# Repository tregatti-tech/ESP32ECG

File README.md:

# ESP32ECG
Open design/code version of ECG device based on esp32

Website https://tregatti.tech
Email info@

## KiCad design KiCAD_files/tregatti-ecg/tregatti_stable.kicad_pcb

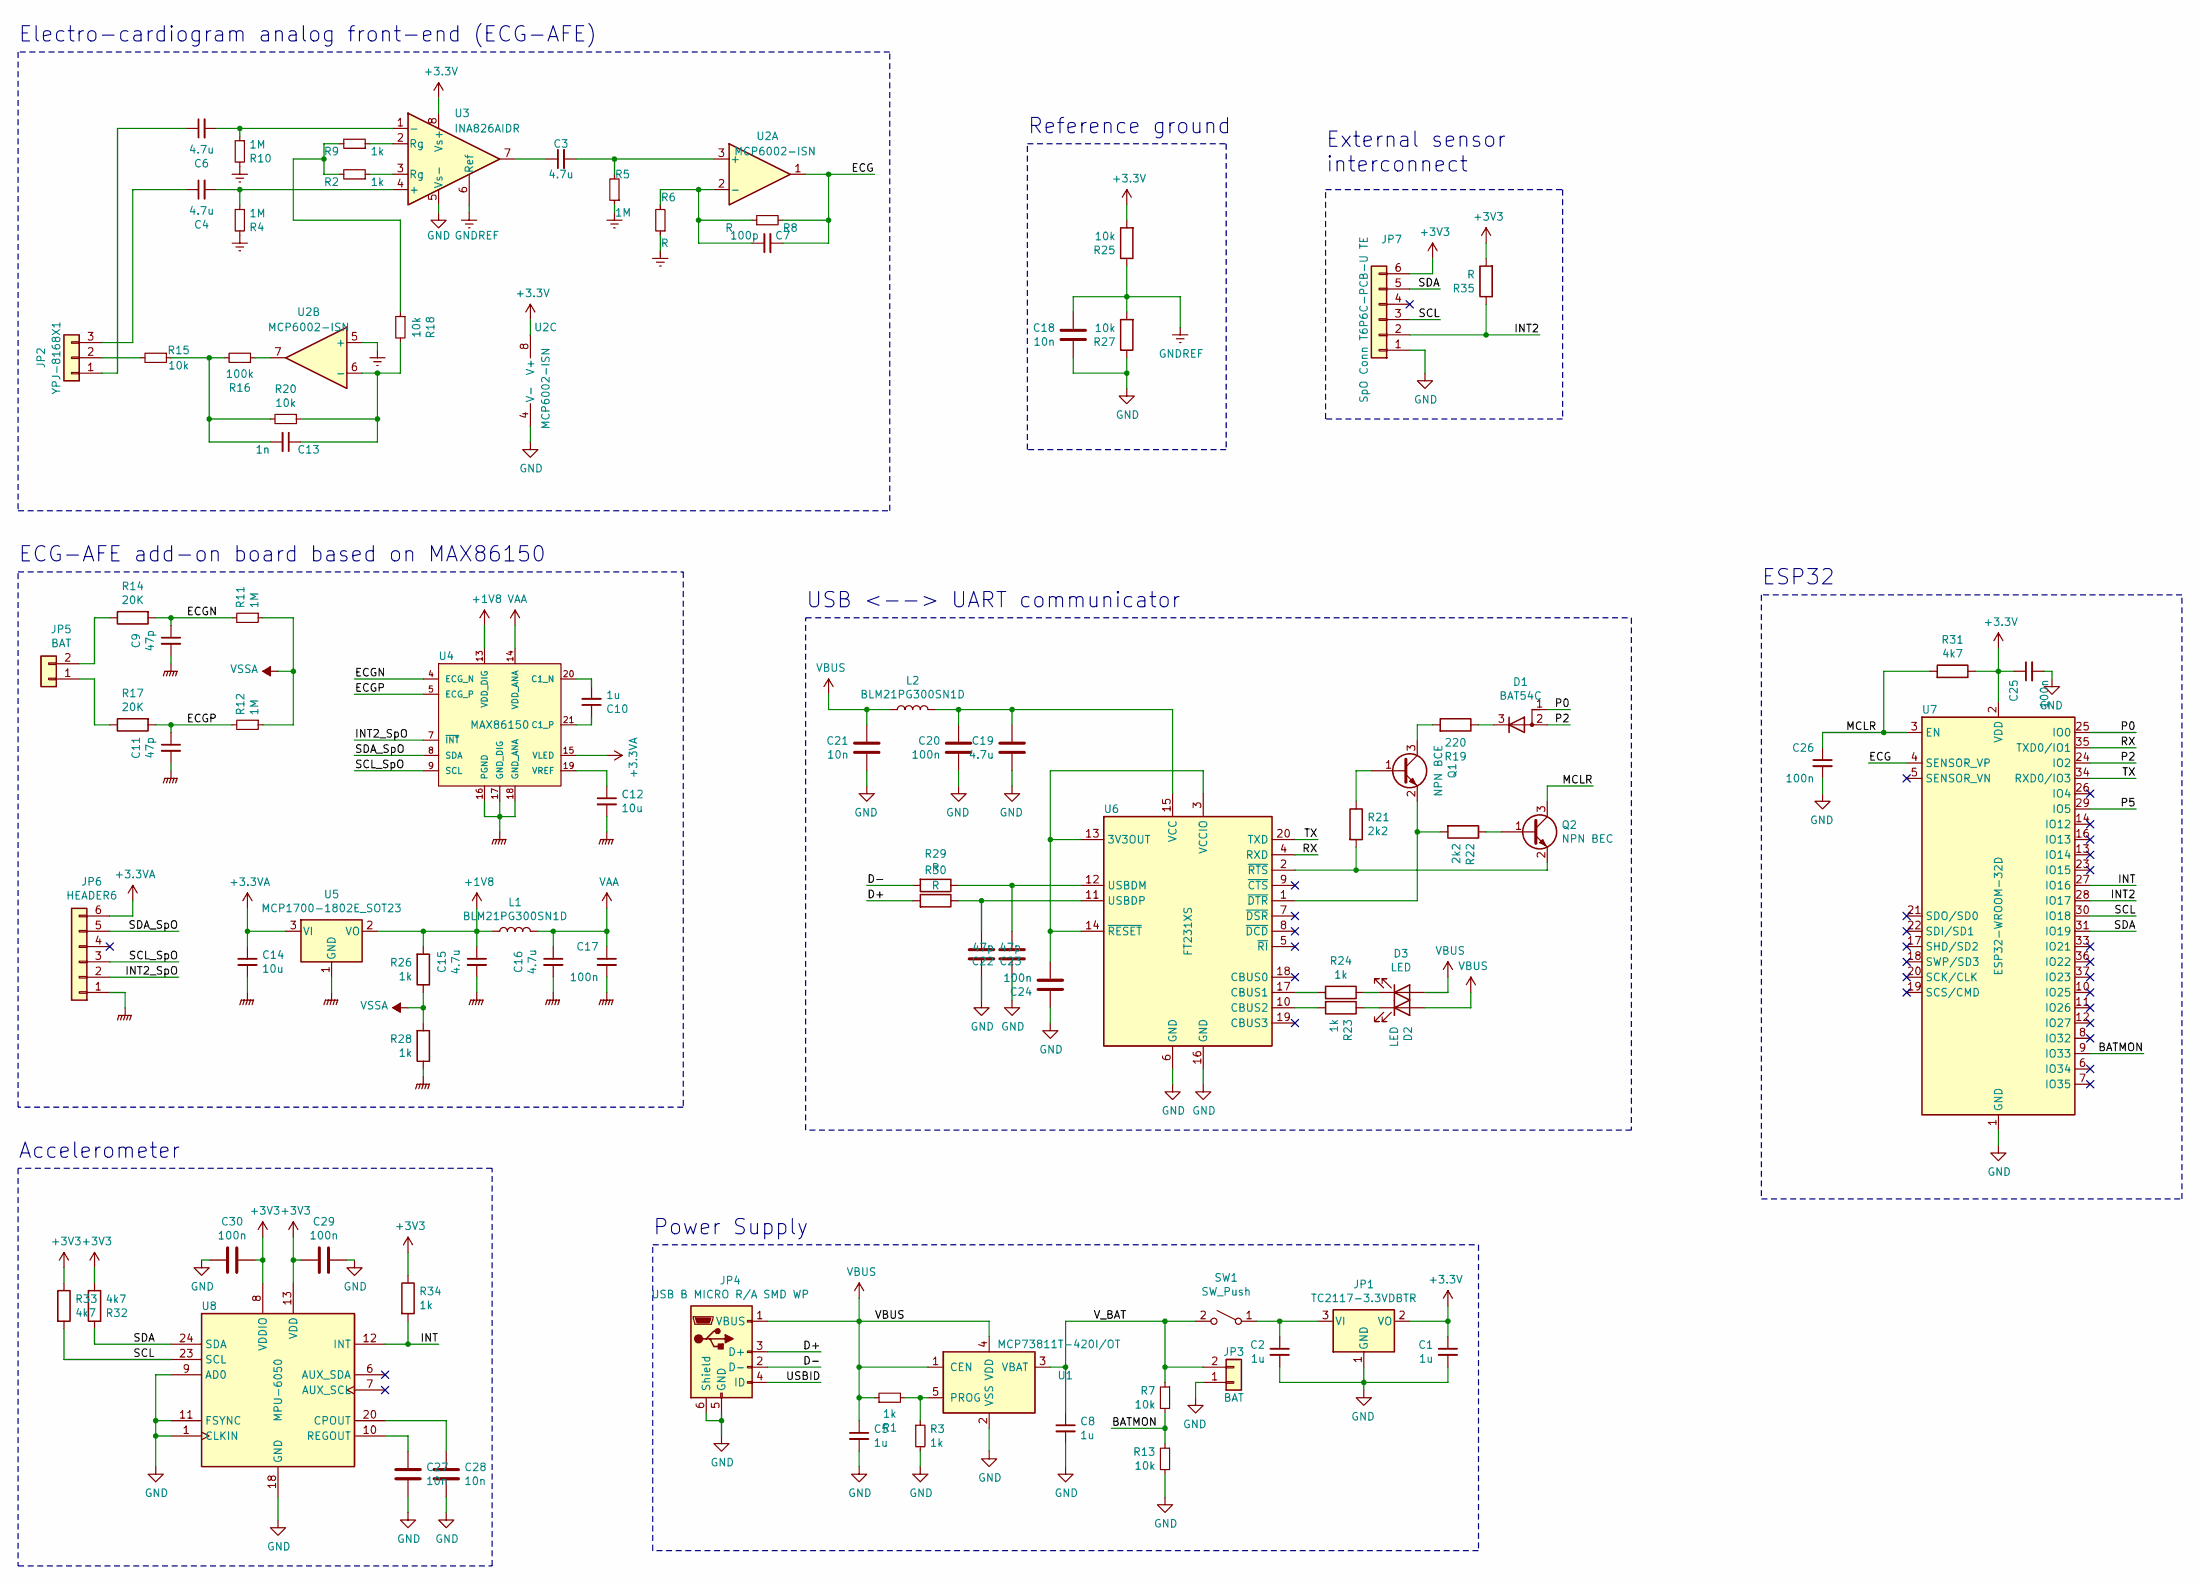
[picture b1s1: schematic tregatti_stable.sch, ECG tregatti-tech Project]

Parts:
C1, C2, C5, C8, C10: 1u; SMD_C0805
C3, C4, C6, C15, C16, C19: 4.7u; SMD_C0805
C7: 100p; SMD_C0805
C9, C11, C22, C23: 47p; SMD_C0805
C12, C14: 10u; SMD_C0805
C13: 1n; SMD_C0805
C17, C20, C24, C25, C26, C29, C30: 100n; SMD_C0805
C18, C21, C27, C28: 10n; SMD_C0805
D1: BAT54C; SMD_SOT23_123
D2, D3: LED; SMD_LED0805
JP1: TC2117-3.3VDBTR; SMD_SOT223
JP2: YPJ-8168X1; AUX_IN_3_5MM_2
JP3, JP5: BAT; SIP_1x2
JP4: USB B MICRO R/A SMD WP; USB_MICRO3
JP6: HEADER6; SIP_1x6
JP7: SpO Conn T6P6C-PCB-U TE; TM.310FACE_6X6
L1, L2: BLM21PG300SN1D; SMD_R0805
Q1: NPN BCE; SMD_SOT23_123
Q2: NPN BEC; SMD_SOT23_123
R1, R2, R3, R9, R23, R24, R26, R28, R34: 1k; SMD_R0805
R4, R5, R10, R11, R12: 1M; SMD_R0805
R6, R8, R29, R30, R35: R; SMD_R0805
R7, R13, R15, R18, R20, R25, R27: 10k; SMD_R0805
R14, R17: 20K; SMD_R0805
R16: 100k; SMD_R0805
R19: 220; SMD_R0805
R21, R22: 2k2; SMD_R0805
R31, R32, R33: 4k7; SMD_R0805
SW1: SW_Push; SWITCH_ONOFF
U1: MCP73811T-420I/OT; SMD_SOT23_5
U2: MCP6002-ISN; SO8_3.9x4.9mm_P1.27mm
U3: INA826AIDR; SO8_3.9x4.9mm_P1.27mm
U4: MAX86150
U5: MCP1700-1802E_SOT23; SMD_SOT23_123
U6: FT231XS; SSOP20_3.9x8.7mm_P0.635mm
U7: ESP32-WROOM-32D; ESP32WROOM
U8: MPU-6050; QFN24_0.50mm_EP4.00mm

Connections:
+1V8: C15.1, L1.1, R26.2, U4.13 (VDD_DIG), U5.2 (VO)
+3.3VA: C14.1, JP6.6, U4.15 (VLED), U5.3 (VI)
/BATMON: R7.2, R13.1, U7.9 (IO33)
/D+: JP4.3 (D+), R30.2
/D-: JP4.2 (D-), R29.2
/ECG: C7.2, R8.2, U2.1, U7.4 (SENSOR_VP)
/ECGN: C9.1, R11.2, R14.2, U4.4 (ECG_N)
/ECGP: C11.1, R12.2, R17.2, U4.5 (ECG_P)
/INT: R34.2, U7.27 (IO16), U8.12 (INT)
/INT2: JP7.2, R35.1, U7.28 (IO17)
/INT2_SpO: JP6.2, U4.7 (~INT~)
/MCLR: C26.1, Q2.3 (C), R31.2, U7.3 (EN)
/P0: D1.1 (A), U7.25 (IO0)
/P2: D1.2 (A), U7.24 (IO2)
/P5: U7.29 (IO5)
/RX: U6.4 (RXD), U7.35 (TXD0/IO1)
/SCL: JP7.3, R33.2, U7.30 (IO18), U8.23 (SCL)
/SCL_SpO: JP6.3, U4.9 (SCL)
/SDA: JP7.5, R32.2, U7.31 (IO19), U8.24 (SDA)
/SDA_SpO: JP6.5, U4.8 (SDA)
/TX: U6.20 (TXD), U7.34 (RXD0/IO3)
/USBID: JP4.4 (ID)
/V_BAT: C8.1, JP3.2, R7.1, SW1.2 (B), U1.3 (VBAT)
GND: C1.2, C2.2, C5.2, C8.2, C18.2, C19.2, C20.2, C21.2, C22.2, C23.2, C24.2, C25.2, C26.2, C27.2, C28.2, C29.2, C30.2, JP1.1 (GND), JP3.1, JP4.5 (GND), JP4.6 (Shield), JP7.1, R3.2, R13.2, R27.1, U1.2 (VSS), U2.4 (V-), U3.5 (Vs-), U6.6 (GND), U6.16 (GND), U7.1 (GND), U7.15 (GND), U7.38 (GND), U7.39 (GND), U8.1 (CLKIN), U8.9 (AD0), U8.11 (FSYNC), U8.18 (GND)
GNDPWR: C9.2, C11.2, C12.2, C14.2, C15.2, C16.2, C17.2, JP6.1, R28.1, U4.16 (PGND), U4.17 (GND_DIG), U4.18 (GND_ANA), U5.1 (GND)
GNDREF: C18.1, R4.2, R5.1, R6.1, R10.2, R25.1, R27.2, U2.5 (+), U3.6 (Ref)
unnamed: C2.1, JP1.3 (VI), SW1.1 (A)
unnamed: C3.1, U3.7
unnamed: C3.2, R5.2, U2.3 (+)
unnamed: C4.1, JP2.3
unnamed: C4.2, R4.1, U3.4 (+)
unnamed: C6.1, JP2.1
unnamed: C6.2, R10.1, U3.1 (-)
unnamed: C7.1, R6.2, R8.1, U2.2 (-)
unnamed: C10.1, U4.21 (C1_P)
unnamed: C10.2, U4.20 (C1_N)
unnamed: C12.1, U4.19 (VREF)
unnamed: C13.1, R18.2, R20.1, U2.6 (-)
unnamed: C13.2, R15.1, R16.2, R20.2
unnamed: C19.1, C20.1, L2.1, U6.15 (VCC)
unnamed: C22.1, R29.1, U6.12 (USBDM)
unnamed: C23.1, R30.1, U6.11 (USBDP)
unnamed: C24.1, U6.3 (VCCIO), U6.13 (3V3OUT), U6.14 (~RESET)
unnamed: C27.1, U8.10 (REGOUT)
unnamed: C28.1, U8.20 (CPOUT)
unnamed: D1.3 (K), R19.1
unnamed: D2.1 (K), R23.1
unnamed: D3.1 (K), R24.1
unnamed: JP2.2, R15.2
unnamed: JP5.1, R17.1
unnamed: JP5.2, R14.1
unnamed: Q1.1 (B), R21.1
unnamed: Q1.2 (E), R22.2, U6.1 (~DTR)
unnamed: Q1.3 (C), R19.2
unnamed: Q2.1 (B), R22.1
unnamed: Q2.2 (E), R21.2, U6.2 (~RTS)
unnamed: R1.2, R3.1, U1.5 (PROG)
unnamed: R2.1, U3.3 (Rg)
unnamed: R9.1, U3.2 (Rg)
unnamed: R16.1, U2.7
unnamed: R2.2, R9.2, R18.1
unnamed: R23.2, U6.10 (CBUS2)
unnamed: R24.2, U6.17 (CBUS1)
VAA: C16.1, C17.1, L1.2, U4.14 (VDD_ANA)
VBUS: C5.1, C21.1, D2.2 (A), D3.2 (A), JP4.1 (VBUS), L2.2, R1.1, U1.1 (CEN), U1.4 (VDD)
VSSA: R11.1, R12.1, R26.1, R28.2

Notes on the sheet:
Accelerometer
USB <--> UART communicator
Power Supply
Electro-cardiogram analog front-end (ECG-AFE)
ECG-AFE add-on board based on MAX86150
ESP32
External sensor interconnect
Reference ground

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
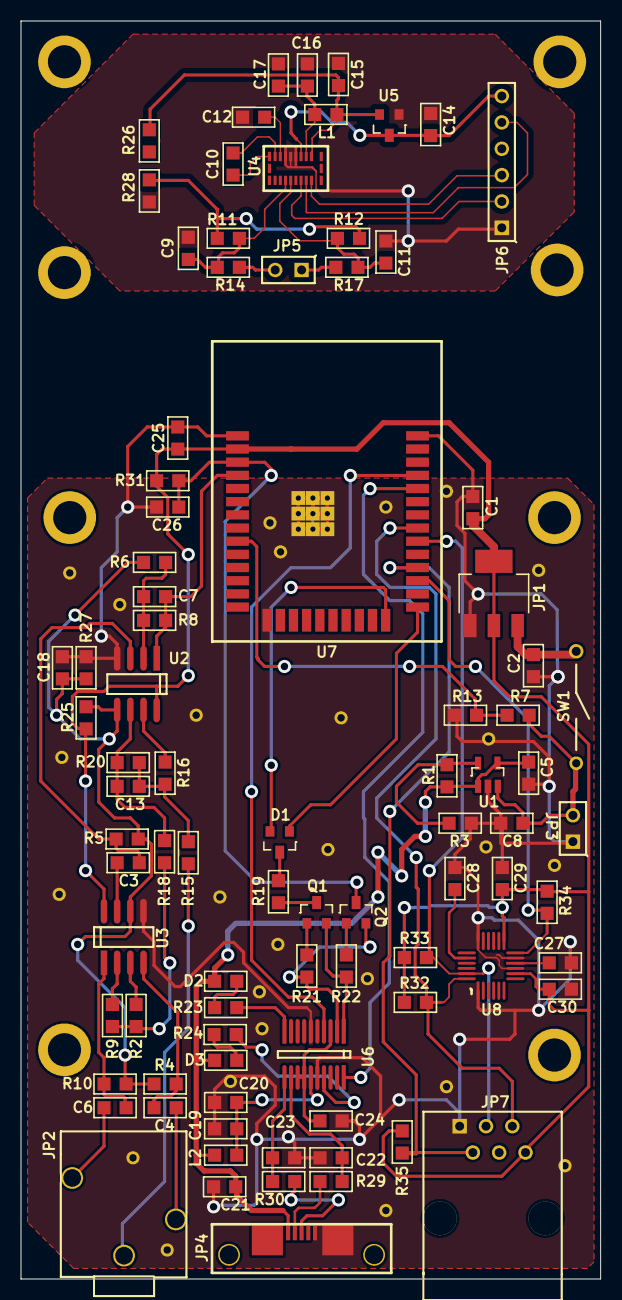
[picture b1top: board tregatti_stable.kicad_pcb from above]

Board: 2 copper layers, 55.9 x 121.3 mm, 121 parts (0 on the bottom side), 65 nets.

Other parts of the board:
89, 90, 91, 92, 93, 94, 95, 96: HOLE_3.2_5
97, 98, 99, 100, 101, 102, 103, 104, 105, 106, 107, 108, 109, 110, 111, 112, 113, 114, 115, 116, 117, 118, 119, 120, 121: HOLE_NO_COPPER

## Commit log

2021-08-14 Presentation for openfest
2021-08-14 STL files for main box and oxymeter
2021-08-14 KiKad version of both board
    //fix copper plates
2021-08-19 Initial bom without ESP-Wroom
    BOM for the project, please note that some component orders are by 10, as it is cheaper this way.
2021-11-17 simple sample
2021-12-08 Moved to folder
2021-12-08 Visualisation previews
2021-12-08 KiCAD design files
2021-12-08 Demo source for openfest
2021-12-08 presentations
2021-12-08 old files
2021-12-10 Front_end added
2021-12-10 add sample data
2021-12-10 add ws_server, modify plotli to plot the data coming from ws server
2021-12-10 add plotly.js in layout.ejs
2021-12-11 add scripts to both ws server and express server, with use of npm run dev and npm run start respectively, PORT in index.js in variable
2021-12-14 Grid and raw ECG drawing on canvas
2021-12-14 add some basic styling
2021-12-14 add imports for the ccs in layout.ejs
2021-12-14 add some basic html for the ecg visualization
2021-12-14 Fixed canvas inside div
2021-12-15 Color change and filtering
2021-12-15 data from server made to arrive in 1000 samples per second, some css fixes
2021-12-16 fixed seconds of data sending intervalfrom 1 to 4, add labelsin css plot
2021-12-17 add an animated css recording button
2021-12-18 add some recording logic (start/stop) to rec-btn click, canvas data to wav file, which is stored on our ws server, needs check and more work
2022-01-17 Changed to d3
2022-01-18 Added RPeak detection and Filtration and BPM
2022-01-22 low-pass-filter button, css and html added only
2022-01-22 low-pass-filter js module added, needs work on injecting it into d3example.js; in d3example.js - formula for heart rate updated
2022-01-27 data for testing changed to original data from device, ws_server updated, client recieving data updated for this purpose
2022-01-27 some additions to styling
2022-01-27 revert ws server and d3example
2022-01-27 Original data used with 2 filters
2022-01-27 Data added
2022-01-27 Low pass filter and RPeak detection updates
2022-01-27 html element for heart beat value, showing correctly original beats from ecg data calcs.
2022-01-28 Refactoring
2022-02-02 Grid with lines and Save recording functionality
2022-02-02 Loading file
2022-02-03 css and html updated, loading and visualizing recording data and grid in offline mode
2022-02-04 added view-section (html, css) on offline mode activation and file loaded, toggling in toggleViewSection.js
2022-02-04 Grid issues fixed
2022-02-04 fix view-section on next-file loaded without page reload
2022-02-04 change view section added in online mode also, but without poincare option
2022-02-04 More grid changes
2022-02-04 RRIntervals array generation
2022-02-04 qrs detection refactored, qRs detector class, Poincare view offline
2022-02-04 style.js file removed from layout.ejs, add toggleButtons style as import in ecgPlotD3
2022-02-05 web socket (ws) changed with socket.io library
2022-02-12 small change in ecgPLotD3.js - receiving data from ws server made only after successful connection
2022-02-18 Last minute changes
2022-06-06 Tux conf presentation
